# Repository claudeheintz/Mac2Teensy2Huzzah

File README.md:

# Mac2Teensy2Huzzah
This is a method for using a Teensy 2.0 or Teensy 2.0++ as a serial bridge so that an Adafruit Huzzah can be programmed from the Arduino IDE on Mac OS X 10.11.

First, load the Mac2Teensy2HuzzahSerialBridge sketch onto the Teensy.  Then, unplug the USB cable from the Mac and connect the Teensy and Huzzah as follows:

Connect V+ and Gnd as well as the serial RX/TX pins.  Note that the RX of the Teensy is connected to TX of the Huzzah and vice-versa.

In addition, the Huzzah's GPIO0 pin should be connected to ground and the GPIO2 pin to +V in order to force the Huzzah into programming mode when it is powered on.  Here is the complete setup ready for the USB cable to be plugged into the Mac.

Full Step-by-Step:
* Load the Mac2Teensy2Huzzah.ino sketch onto the Teensy.
* Unplug the USB cable and connect the Teensy to the Huzzah as shown.
* Switch to your sketch that you want to load on the Huzzah
* Don't forget to change to Tools->Board: "Adafruit HUZZAH ESP8266".  The Teensy's serial port should still be selected in Tools->Port.
* Plug the USB cable into the Mac and click "Upload".
* After the sketch compiles, you should see the Teensy's LED light up as the program is uploaded to the Huzzah's flash.
* Once the upload is complete, be sure to disconnect GPIO0 from ground and GPIO2 from V+.

Eagle files are included for making a permanent programmer setup with a Teensy 2.0:

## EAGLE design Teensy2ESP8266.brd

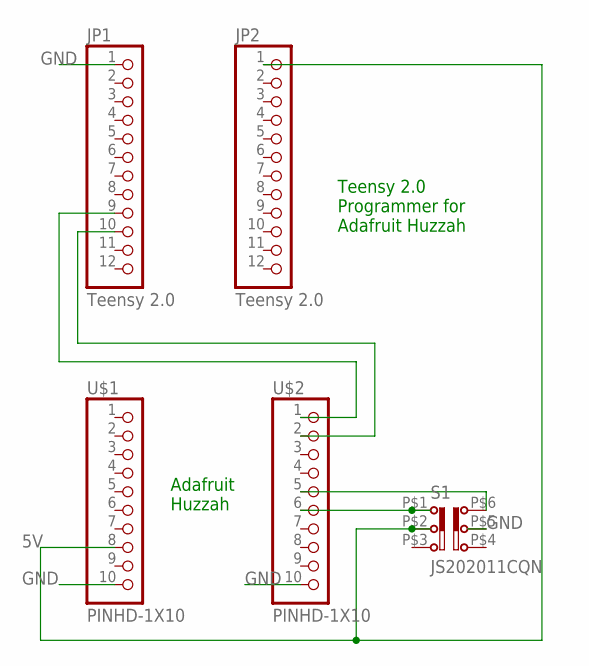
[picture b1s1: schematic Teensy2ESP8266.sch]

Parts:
JP1, JP2: Teensy 2.0; 1X12
S1: JS202011CQN
U$1, U$2: PINHD-1X10; 1X10-BIG

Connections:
5V: JP2.1, S1.P$2 (2), U$1.8
GND: JP1.1, S1.P$5 (5), U$1.10, U$2.10
unnamed: S1.P$1 (1), U$2.6
unnamed: S1.P$6 (4), U$2.5
RX2: JP1.9, U$2.1
TX2: JP1.10, U$2.2

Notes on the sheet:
Adafruit Huzzah
Teensy 2.0 Programmer for Adafruit Huzzah

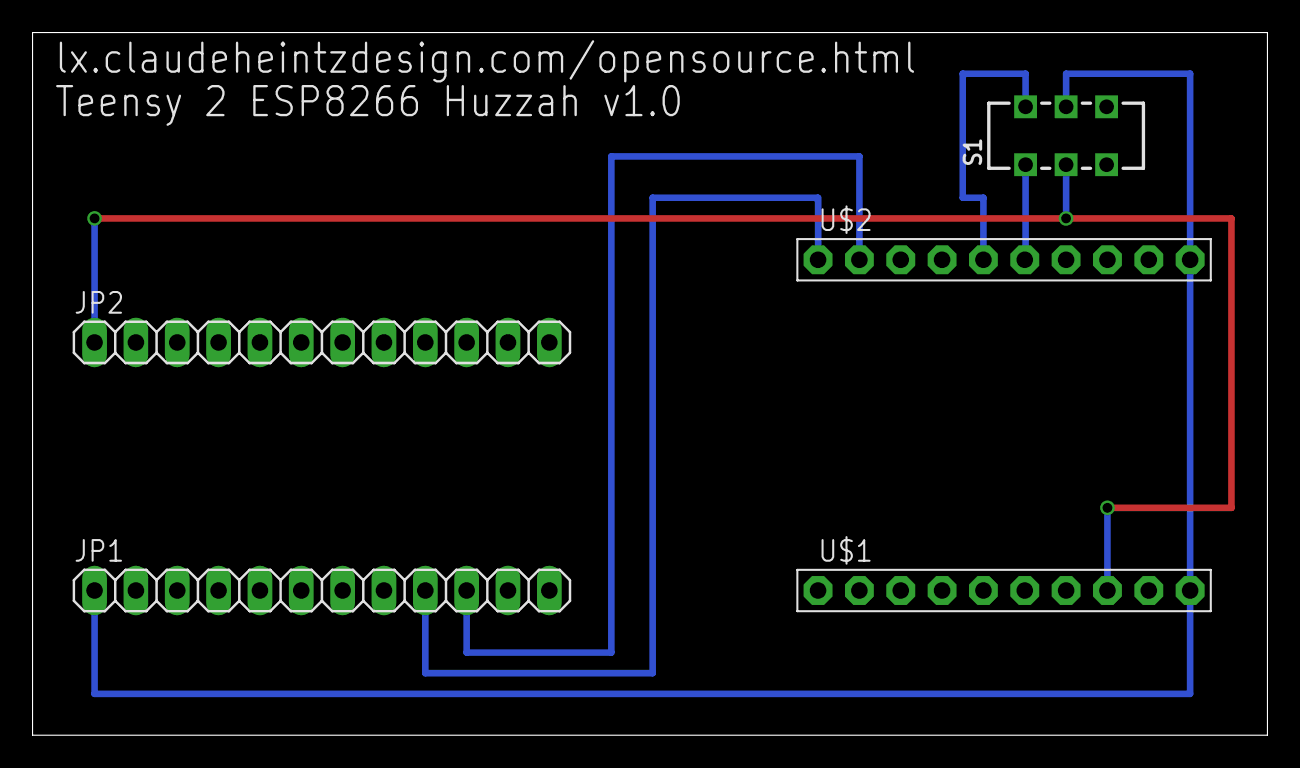
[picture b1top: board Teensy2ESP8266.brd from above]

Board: 2 copper layers, 75.9 x 43.2 mm, 5 parts (0 on the bottom side), 6 nets.

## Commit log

2015-12-18 fixed diagram
2016-04-13 Added Eagle Files
2016-04-13 reduced photo size
2016-04-13 small edit

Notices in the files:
parts and their libraries:
switch-ck: Copyright (C) 2011, Bob Starr
